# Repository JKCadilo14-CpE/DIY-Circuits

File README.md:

# DIY Circuits

A curated collection of beginner-friendly KiCad PCB projects designed for learning, experimentation, and educational reference.

This repository contains editable KiCad circuit projects for students, hobbyists, and junior engineers practicing schematic capture, PCB layout, and basic electronics documentation. Each documented project has its own README with circuit notes, source-file navigation, beginner guidance, and project-specific safety reminders.

| Repository detail | Status |
| --- | --- |
| Educational focus | Low-voltage KiCad PCB learning projects |
| KiCad metadata | KiCad 9.0 and 10.0 generator versions detected |
| Documented transistor-based projects | 12 |
| Documented project READMEs | 12 |
| Hardware-tested transistor projects | 12 |
| License | [MIT License](LICENSE) |

## Educational Use Notice

This repository is intended for educational and personal learning purposes. The circuits, schematics, PCB layouts, fabrication files, and documentation are shared to help students understand electronics design, PCB fabrication, and circuit analysis.

Please do not submit these projects as your own academic work. If you use any design or idea from this repository, make sure you understand how it works, adapt it to your own requirements, and follow your institution's academic integrity policies.

The goal of this repository is to encourage learning, experimentation, and skill development—not to replace your own design process.

## Academic Integrity

If you are using this repository for a class, use it as a reference to understand concepts and improve your own designs. Always create and submit work that complies with your instructor's requirements and your institution's academic integrity policies.

## Who This Repository Is For

- Students learning PCB design with KiCad.
- Beginners studying transistor-based circuits and simple sensor interfaces.
- Hobbyists building educational low-voltage electronics projects.
- Readers who want editable KiCad examples instead of static screenshots only.

## Repository Highlights

- Editable KiCad project, schematic, and PCB source files.
- Project-level documentation for each active documented circuit.
- Beginner-friendly notes, learning objectives, and common build checks.
- Documented prototype hardware-tested status in project READMEs.
- MIT-licensed educational reference material.

## Category Overview

| Category | Current Documentation Status | Link |
| --- | --- | --- |
| Transistor Based | Version 2.0.0 category README with 12 documented projects | [Open category](<Transistor Based/README.md>) |
| Arduino | Folder present; project documentation may be added in future phases | [Open folder](Arduino/) |
| ESP32 | Folder present; project documentation may be added in future phases | [Open folder](ESP32/) |
| Power Supply | Folder present; project documentation may be added in future phases | [Open folder](<Power Supply/>) |
| Raspberry Pi | Folder present; project documentation may be added in future phases | [Open folder](<Raspberry Pi/>) |
| Sensor Modules | Folder present; project documentation may be added in future phases | [Open folder](<Sensor Modules/>) |
| Docs | Repository documentation folder | [Open folder](Docs/) |
| Project Templates | Template/reference folder | [Open folder](<Project Templates/>) |

## Featured Projects

| Project | Why it is useful | Difficulty | Hardware Tested | Link |
| --- | --- | --- | --- | --- |
| Water Level Indicator | Multi-stage sensing and indication project with LEDs and buzzer output. | Beginner–Intermediate | Yes | [Open README](<Transistor Based/water level indicator/README.md>) |
| Temperature Controlled DC Fan - BC547 | Thermistor-based fan-control example using a transistor driver stage. | Beginner | Yes | [Open README](<Transistor Based/temperature controlled dc fan - BC547/README.md>) |
| Automatic Hand Sanitizer | Sensor-controlled pump-switching project for load-control practice. | Intermediate | Yes | [Open README](<Transistor Based/automatic hand sanitizer/README.md>) |
| Laser Alarm Security Circuit | Optical interruption alarm example using an LDR, LED, and buzzer. | Intermediate | Yes | [Open README](<Transistor Based/Laser Alarm Security Circuit/README.md>) |
| Astable Multivibrator Circuit | Classic two-transistor LED flasher for timing and feedback concepts. | Beginner | Yes | [Open README](<Transistor Based/astable miltivibrator Circuit/README.md>) |
| 9V Battery Status Indicator Circuit | Simple voltage-indicator project using LEDs, zener reference, and transistors. | Beginner | Yes | [Open README](<Transistor Based/9V Battery Status Indicator Circuit/README.md>) |

## Complete Project Catalog

The Version 2.0.0 documented project catalog currently covers the transistor-based category.

| Project | Category | Difficulty | Hardware Tested | Documentation | Link |
| --- | --- | --- | --- | --- | --- |
| 9V Battery Status Indicator Circuit | Voltage indication | Beginner | Yes | README available | [Open](<Transistor Based/9V Battery Status Indicator Circuit/README.md>) |
| Astable Multivibrator Circuit | Timing / oscillator | Beginner | Yes | README available | [Open](<Transistor Based/astable miltivibrator Circuit/README.md>) |
| Light-Activated Switch Circuit | Light-activated switching | Beginner | Yes | README available | [Open](<Transistor Based/Light-Activated Switch Circuit/README.md>) |
| Temperature Controlled DC Fan - BC547 | Temperature control | Beginner | Yes | README available | [Open](<Transistor Based/temperature controlled dc fan - BC547/README.md>) |
| Laser Alarm Security Circuit | Optical alarm | Intermediate | Yes | README available | [Open](<Transistor Based/Laser Alarm Security Circuit/README.md>) |
| Fire Alarm System Using Photodiode | Optical alarm | Intermediate | Yes | README available | [Open](<Transistor Based/fire alarm system using photodiode/README.md>) |
| Obstacle Detector | IR obstacle sensing | Intermediate | Yes | README available | [Open](<Transistor Based/obstacle detector/README.md>) |
| Touch Sensor Circuit | Touch sensing | Beginner–Intermediate | Yes | README available | [Open](<Transistor Based/touch sensor circuit/README.md>) |
| Clap Switch Circuit | Sound-triggered switching | Intermediate | Yes | README available | [Open](<Transistor Based/clap switch circuit/clap switch circuit/README.md>) |
| Automatic Hand Sanitizer | Sensor-controlled load | Intermediate | Yes | README available | [Open](<Transistor Based/automatic hand sanitizer/README.md>) |
| Hidden Wire Detector | Detection / sensing | Intermediate | Yes | README available | [Open](<Transistor Based/Hidden Wire Detector/README.md>) |
| Water Level Indicator | Water-level sensing | Beginner–Intermediate | Yes | README available | [Open](<Transistor Based/water level indicator/README.md>) |

## Learning Path

Start with the simpler indicator and timing circuits, then move into sensor-driven and multi-stage projects:

1. 9V Battery Status Indicator Circuit
2. Astable Multivibrator Circuit
3. Light-Activated Switch Circuit
4. Temperature Controlled DC Fan - BC547
5. Laser Alarm Security Circuit
6. Fire Alarm System Using Photodiode
7. Obstacle Detector
8. Touch Sensor Circuit
9. Clap Switch Circuit
10. Automatic Hand Sanitizer
11. Hidden Wire Detector
12. Water Level Indicator

See the [Transistor Based category README](<Transistor Based/README.md>) for the category index, common build checks, and category-level safety notes.

## Repository Statistics

| Statistic | Detected value |
| --- | --- |
| Documented transistor-based projects | 12 |
| Project READMEs in `Transistor Based/` | 12 |
| Hardware-tested transistor projects | 12 |
| KiCad generator versions | 9.0, 10.0 |
| License file | MIT License present |
| Circuit categories | Voltage indication, timing, light sensing, optical alarm, IR sensing, touch sensing, sound switching, load control, wire detection, water-level sensing |

## Future Roadmap

- Add more finished hardware photographs where available.
- Continue improving project galleries and 3D board renders.
- Add BOMs, assembly notes, and manufacturing packages in a later release phase.
- Expand educational explanations without duplicating project READMEs.
- Extend Version 2.0.0 documentation standards to additional repository categories after review.

## Contributing

Documentation improvements, educational suggestions, bug reports, and pull requests are welcome. Please keep changes clear, evidence-based, and beginner-friendly.

## Safety

These projects are intended for low-voltage electronics learning. Do not connect them to mains electricity or use them as certified alarm, safety, medical, life-support, or mission-critical equipment. Review each design carefully before building or modifying it.

## License

This repository is available under the [MIT License](LICENSE).

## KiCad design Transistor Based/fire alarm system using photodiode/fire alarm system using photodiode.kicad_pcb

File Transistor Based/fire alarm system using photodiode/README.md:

# Fire Alarm System Using Photodiode

A beginner-friendly photodiode alarm project that demonstrates how light from a flame can activate a transistor-driven LED and buzzer output.

## Project Information

| Item | Details |
| --- | --- |
| Status | Educational Prototype |
| Difficulty | Intermediate |
| Hardware Tested | Breadboard and PCB prototype assembled and functionally tested |
| Supply Voltage | Prototype tested with a 9V battery; exact operating range not characterized |
| KiCad Compatibility | KiCad 10.0 metadata |
| License | MIT License |

## Project Overview

This project demonstrates an educational optical fire-alarm concept using a photodiode, BC547 transistor, LED, and buzzer. Light from a flame reaches the photodiode, the photodiode changes the sensing condition, the transistor stage responds, and the LED/buzzer output path activates.

This README documents the photodiode implementation shown in the KiCad schematic. A thermistor-based version could be explored as a future modification, but this README documents the verified photodiode implementation.

This project is intended for educational demonstration only and must not be relied upon as a fire detection, fire alarm, or life-safety device.

## Features

- Photodiode-based optical sensing input.
- Single BC547 transistor stage.
- LED visual output.
- Buzzer audible output.
- Beginner-friendly example of sensor polarity, transistor orientation, and resistor verification.
- Existing schematic, PCB layout images, 3D render, editable KiCad files, and B.Cu PDF export.

## Applications

- Educational photodiode alarm demonstrations.
- Introductory transistor switching exercises.
- Low-voltage optical sensor laboratory activities.
- Breadboard-to-PCB comparison practice.
- Soldering, continuity, and cold-joint troubleshooting exercises.
- Demonstrations of how ambient light can influence optical sensor circuits.

## Components Used

| Reference | Component | Role in the Circuit |
| --- | --- | --- |
| J1 | `input` connector | Provides the circuit input connection shown in the schematic. |
| BZ1 | Buzzer | Audible output device in the alarm output path. |
| D1 | LED | Visual output indicator. |
| D2 | `D_Photo` photodiode | Optical sensor input that responds to light reaching its surface. |
| Q1 | BC547 transistor | Transistor stage that responds to the photodiode sensing condition. |
| R1 | Schematic resistor value | Resistor in the sensing/output network; use the value documented in the schematic for the verified build. |

## Circuit Explanation

The schematic uses D2 as the photodiode input. When light reaches the photodiode, the sensing condition changes and affects the bias at Q1.

Q1 is a BC547 transistor stage connected to the LED and buzzer output path. When the transistor stage responds to the photodiode condition, D1 and BZ1 provide visible and audible indication.

R1 is shown in the schematic with its documented value. Because the schematic label is the repository evidence for this build, verify the resistor value against the schematic before assembly instead of guessing or substituting parts.

This circuit is an educational optical alarm demonstration. It does not document a measured flame-detection distance, sensing angle, response time, temperature threshold, light-intensity threshold, or output current.

## Theory

A photodiode is a light-sensitive semiconductor device. In this project, it is used as the optical input device for a transistor alarm stage. Light from a flame can reach the photodiode and change the condition applied to the transistor stage.

A BC547 transistor can be used as a small-signal switching stage. The transistor does not measure fire or temperature directly; it responds to the electrical condition created by the photodiode and surrounding resistor network.

Ambient light can also influence a photodiode. This is why testing should be performed under controlled indoor lighting, and why unwanted LED glow can be diagnosed by covering the photodiode.

The photodiode approach is different from a temperature-based alarm. A thermistor-based version could be explored as a future modification, but this README documents the verified photodiode implementation.

## How It Works

1. A 9V battery is connected to J1 with correct polarity.
2. The photodiode is exposed to the intended optical test source.
3. Light from a flame reaches the photodiode.
4. The photodiode changes the sensing condition at the transistor stage.
5. Q1 responds to that sensing condition.
6. The LED and buzzer output path activates.

This section describes the intended photodiode alarm concept from the schematic. Physical prototype observations, including flashlight activation during testing, are documented separately under **Verified Prototype Observations**.

## Project Gallery

### Schematic

### PCB Layout Top

### PCB Layout Bottom

### 3D PCB Render

### Finished Hardware

> Finished hardware photographs will be added after the completed prototype is photographed.

## Assembly Guide

1. Review the schematic and PCB layout before soldering.
2. Install R1 after verifying the resistor value against the schematic.
3. Install D2, confirming photodiode polarity.
4. Install D1, confirming LED polarity.
5. Install Q1 after checking the BC547 emitter, base, and collector pinout.
6. Install BZ1, confirming the selected buzzer is appropriate for the build.
7. Install the input connector.
8. Inspect all solder joints and PCB copper traces before applying power.
9. Perform continuity checks before connecting the battery.

## Before You Power the Circuit

| Check | What to Verify |
| --- | --- |
| Battery polarity | Confirm correct supply polarity before connection. |
| Transistor orientation | Confirm Q1 matches the BC547 pinout expected by the PCB footprint. |
| Photodiode polarity | Confirm D2 orientation before applying power. |
| LED polarity | Confirm D1 anode/cathode orientation. |
| Resistor value | Verify R1 against the schematic before assembly. |
| Buzzer connection | Confirm BZ1 is connected in the intended output location. |
| PCB copper traces | Inspect for oxidation, contamination, or visible damage. |
| Solder bridges | Inspect adjacent pads and traces for accidental shorts. |
| Continuity test | Check for unintended shorts before connecting a battery. |

## Testing

This project is intended for educational demonstration only and must not be relied upon as a fire detection, fire alarm, or life-safety device. Flame testing should be performed only with a small controlled flame source, appropriate supervision, and safe surroundings.

Suggested test procedure:

1. Inspect the PCB under good lighting.
2. Confirm 9V battery polarity before connection.
3. Check battery voltage with a multimeter if behavior is inconsistent.
4. Verify Q1 transistor orientation.
5. Verify D2 photodiode polarity.
6. Verify D1 LED polarity.
7. Verify the R1 value against the schematic.
8. Test indoors under controlled lighting before introducing a flame source.
9. Perform a conservative flame-response demonstration and observe the LED/buzzer response.
10. Use a mobile phone flashlight only as a prototype-observed optical response check, not as the intended design description.
11. Evaluate whether ambient light causes unwanted LED glow or false triggering.
12. Compare PCB behavior with the verified breadboard prototype if unexpected behavior occurs.
13. Disconnect power immediately if any component becomes unusually warm.

Successful test indicators:

- The board powers without short-circuit symptoms.
- The circuit responds during the intended educational optical demonstration.
- Unwanted LED glow can be explained by ambient light rather than a wiring fault.
- PCB behavior is consistent with the breadboard prototype after assembly issues are corrected.

## Practical Build Notes

### Prototype Notes

The following items are **Verified Prototype Observations** from the physical build. They extend beyond what is explicitly guaranteed by the KiCad schematic.

- Breadboard prototype required several rounds of troubleshooting before operating correctly.
- Incorrect resistor selection and wiring mistakes that affected the intended circuit power distribution initially prevented proper operation.
- Breadboard prototype eventually operated as intended.
- PCB prototype was assembled and successfully tested.
- Prototype was powered using a 9V battery.
- During prototype testing, light from a flame activated the circuit.
- During prototype testing, a mobile phone flashlight also activated the circuit.
- PCB prototype initially experienced photodiode sensitivity issues and cold solder joints.
- During prototype testing, increasing the resistor value associated with the photodiode sensing stage reduced unwanted triggering caused by ambient light in this specific prototype.
- During prototype testing, the LED occasionally glowed dimly because the photodiode responded to surrounding light.
- Covering the photodiode removed the unwanted LED illumination, indicating that surrounding ambient light not a wiring fault was causing the unwanted sensor response during prototype testing.

### Photodiode Sensitivity Notes

Photodiodes may respond to surrounding ambient light. Test indoors under controlled lighting conditions, and avoid direct sunlight or other intense light sources that may cause unintended activation.

The resistor-value change described above is a verified prototype observation, not the documented schematic configuration. Retain the resistor value shown in the schematic unless intentionally redesigning and revalidating the sensing stage.

This README does not recommend resistor substitutions.

### Photodiode vs Thermistor Note

A thermistor-based version could be explored as a future modification, but this README documents the verified photodiode implementation.

Do not assume a thermistor version has been verified for this project unless a future schematic, PCB, and tested prototype explicitly document that change.

### Builder Recommendations

- Verify transistor orientation using the datasheet.
- Verify photodiode polarity and LED polarity before soldering.
- Verify the resistor value against the schematic before assembly. Use the documented schematic value for the verified build.
- Breadboard-test before PCB assembly whenever possible.
- Inspect solder joints carefully.
- Inspect PCB copper traces for oxidation, contamination, or damage.
- Compare PCB behavior with the verified breadboard prototype.
- Make only one circuit modification at a time during troubleshooting, then retest before changing additional components.
- If the LED glows dimly unexpectedly, cover the photodiode to determine whether ambient light is influencing the circuit.
- Disconnect power immediately if components become unusually warm, then verify polarity, transistor orientation, resistor value, and solder quality before testing again.

## Troubleshooting

| Symptom | Checks |
| --- | --- |
| Circuit does not respond to flame | Check battery polarity and voltage, photodiode polarity, Q1 orientation, R1 value, solder joints, and whether the flame test is safely positioned for the photodiode to receive light. |
| Circuit responds to flashlight but not flame | Recheck the flame demonstration setup, photodiode orientation, ambient lighting, and breadboard comparison; do not infer a certified fire-detection capability. |
| LED glows dimly without a flame | Cover the photodiode completely, reduce ambient lighting, verify photodiode polarity, inspect the resistor value associated with the photodiode sensing stage, check solder joints, and compare behavior with the verified breadboard prototype. |
| False triggering from ambient light | Test under controlled indoor lighting, avoid direct sunlight or intense light sources, and cover the photodiode to confirm whether ambient light is influencing the circuit. |
| Incorrect transistor orientation | Check the BC547 datasheet and confirm emitter, base, and collector match the PCB footprint. |
| Incorrect photodiode polarity | Confirm D2 orientation and reinstall correctly if needed. |
| Wrong resistor value | Verify R1 against the schematic and compare with the breadboard prototype. |
| Cold solder joints | Reinspect dull, cracked, or incomplete solder joints after disconnecting power. |
| Breadboard works but PCB does not | Compare PCB assembly against the verified breadboard prototype, then inspect solder bridges, cold solder joints, copper trace condition, component polarity, and resistor placement. |
| Buzzer or LED output does not activate | Check BZ1 and D1 connections, Q1 orientation, photodiode polarity, R1 value, solder joints, and battery condition. |

If covering the photodiode completely causes the LED to turn off, the sensor is responding to ambient light rather than a wiring fault.

## Downloads

| File | Description |
| --- | --- |
| [`fire alarm system using photodiode.kicad_pro`](<fire alarm system using photodiode.kicad_pro>) | KiCad project file. Open this file in KiCad. |
| [`fire alarm system using photodiode.kicad_sch`](<fire alarm system using photodiode.kicad_sch>) | KiCad schematic source. |
| [`fire alarm system using photodiode.kicad_pcb`](<fire alarm system using photodiode.kicad_pcb>) | KiCad PCB layout source. |
| [`fire alarm system using photodiode-B_Cu.pdf`](<fire alarm system using photodiode-B_Cu.pdf>) | Existing B.Cu PDF plot export. |

## Educational Use Notice

This repository is intended for educational and personal learning purposes. The circuits, schematics, PCB layouts, fabrication files, and documentation are shared to help students understand electronics design, PCB fabrication, and circuit analysis.

Please do not submit these projects as your own academic work. If you use any design or idea from this repository, make sure you understand how it works, adapt it to your own requirements, and follow your institution's academic integrity policies.

The goal of this repository is to encourage learning, experimentation, and skill development—not to replace your own design process.

## Academic Integrity

If you are using this repository for a class, use it as a reference to understand concepts and improve your own designs. Always create and submit work that complies with your instructor's requirements and your institution's academic integrity policies.

## Revision History

| Version | Changes |
| --- | --- |
| 2.0.0 | Updated README to follow the Version 2.0.0 documentation standard with expanded project information, circuit explanation, theory, assembly guidance, testing notes, practical build notes, troubleshooting, gallery, downloads, and repository notices. |

## License

This project is released under the MIT License. See the repository [LICENSE](../../LICENSE).

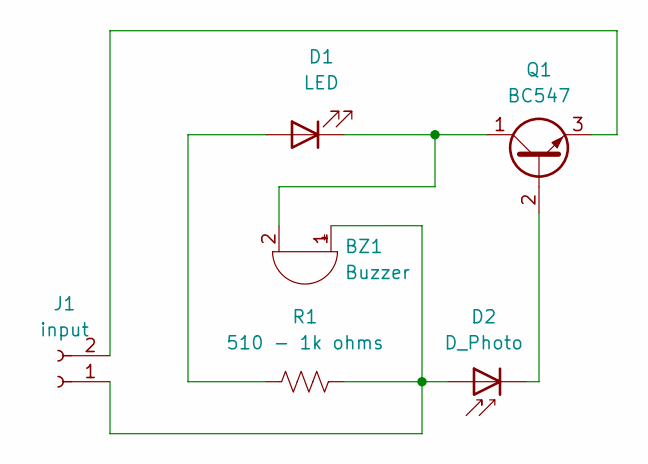
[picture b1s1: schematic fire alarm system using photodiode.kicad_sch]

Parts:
BZ1: Buzzer; Buzzer_15x7.5RM7.6
D1: LED; LED_D5.0mm
D2: D_Photo; LED_D5.0mm_IRBlack
J1: input; TerminalBlock_Phoenix_MKDS-1,5-2_1x02_P5.00mm_Horizontal
Q1: BC547; TO-92_Inline
R1: 510 - 1k ohms; R_Axial_DIN0207_L6.3mm_D2.5mm_P10.16mm_Horizontal

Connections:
unnamed: BZ1.1 (+), D2.2 (A), J1.1, R1.2
unnamed: BZ1.2 (-), D1.1 (K), Q1.1 (C)
unnamed: D1.2 (A), R1.1
unnamed: D2.1 (K), Q1.2 (B)
unnamed: J1.2, Q1.3 (E)

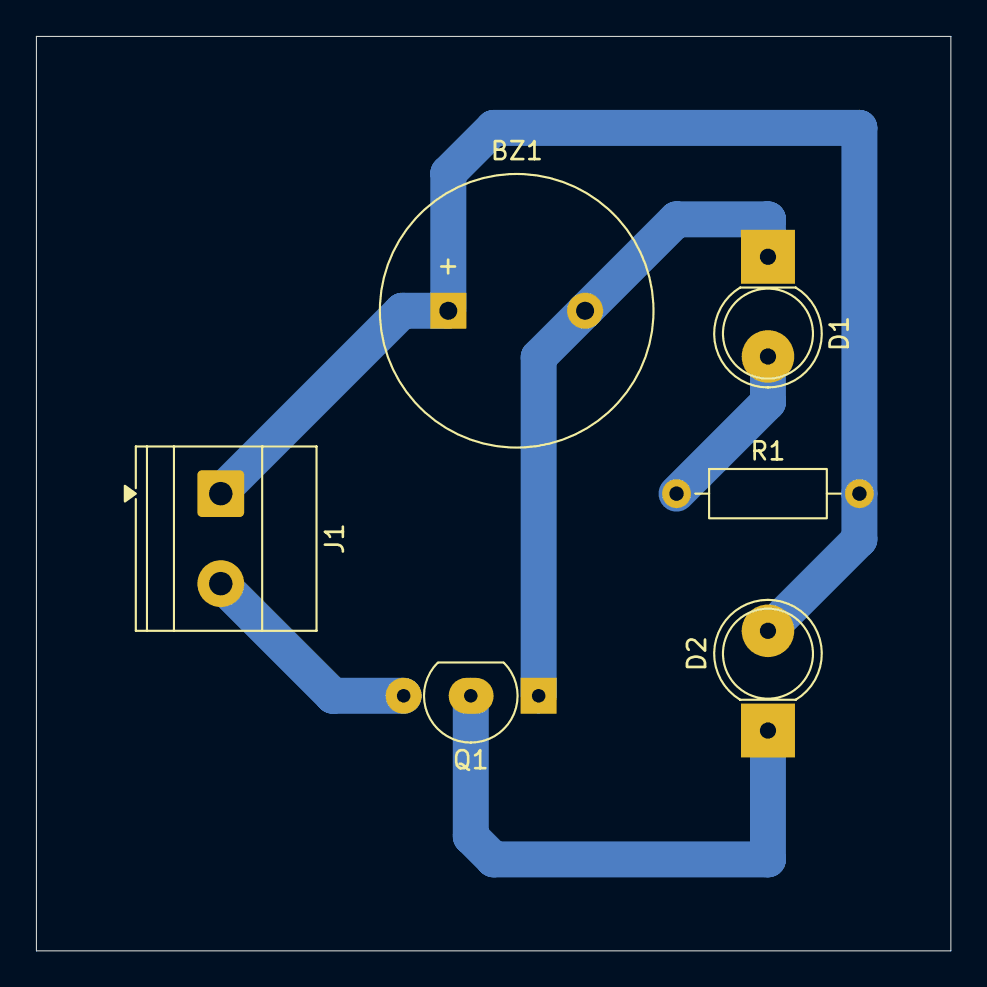
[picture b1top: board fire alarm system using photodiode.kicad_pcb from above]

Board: 2 copper layers, 50.8 x 50.8 mm, 6 parts (0 on the bottom side), 5 nets.

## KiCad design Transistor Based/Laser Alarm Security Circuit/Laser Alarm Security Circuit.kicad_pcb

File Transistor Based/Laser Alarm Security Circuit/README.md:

# Laser Alarm Security Circuit

A beginner-friendly laser-interruption alarm project using an LDR, BC547 transistor, LED, buzzer, and an external laser source for demonstration.

## Project Information

| Item | Details |
| --- | --- |
| Status | Educational Prototype |
| Difficulty | Intermediate |
| Hardware Tested | Breadboard and PCB prototype assembled and functionally tested |
| Supply Voltage | Prototype tested with a 9V battery; exact operating range not characterized |
| KiCad Compatibility | KiCad 10.0 metadata |
| License | MIT License |

## Project Overview

This project demonstrates an educational optical beam-interruption alarm. An external laser module projects a beam onto the LDR. The LDR and R2 form a light-dependent input condition for Q1. When the beam is interrupted, the LDR condition changes, Q1 responds, and D1/BZ1 provide visible and audible alarm indication.

The laser module used during prototype testing served only as the optical source. It is not part of the PCB schematic.

This project is intended for educational demonstration only and must not be relied upon as a real security or intrusion detection system.

## Features

- LDR-based optical sensing input.
- External laser beam used as the demonstration light source.
- Single BC547 transistor stage.
- LED visual output.
- Buzzer audible output.
- Beginner-friendly example of alignment-sensitive optical sensing.
- Existing schematic, PCB layout images, 3D render, editable KiCad files, and B.Cu PDF export.

## Applications

- Educational laser-interruption alarm demonstrations.
- LDR and fixed-resistor sensing exercises.
- Transistor switching laboratory activities.
- Optical alignment and interruption testing practice.
- Breadboard-to-PCB comparison practice.
- Soldering and cold-joint troubleshooting exercises.

## Components Used

| Reference | Component | Role in the Circuit |
| --- | --- | --- |
| J1 | `input` connector | Provides the main circuit input connection shown in the schematic. |
| J2 | `laser_input` connector | Schematic connector associated with the laser input connection. |
| R1 | `LDR03` | Light-dependent resistor used as the optical sensing element. |
| R2 | 10K ohm resistor | Fixed resistor used with the LDR to form the light-dependent input condition. |
| Q1 | BC547 transistor | Transistor stage that responds to the LDR sensing condition. |
| D1 | LED | Visual output indicator. |
| BZ1 | Buzzer | Audible output indicator. |

## Circuit Explanation

The schematic uses R1 as an LDR and R2 as a 10K ohm resistor. Together, they form a light-dependent input condition for Q1.

When the external laser beam is centered on the LDR, the LDR is illuminated and the circuit remains in its normal beam-present state. When an object interrupts the beam, the light reaching the LDR changes. That change affects the transistor stage, which drives the LED and buzzer output path.

Q1 is a BC547 transistor. Correct transistor orientation matters because the emitter, base, and collector must match the PCB footprint.

The external laser module is used as the optical source for testing and demonstration. The repository schematic documents the PCB circuit; it does not characterize laser power, detection distance, beam interruption distance, response time, or sensitivity range.

## Theory

An LDR, or light-dependent resistor, changes resistance as the light reaching its surface changes. In this project, the LDR is aimed at a laser beam so the circuit can respond when the beam is present or interrupted.

R2 works with the LDR to create a light-dependent input condition. Q1 responds to that condition and controls the output path for the LED and buzzer.

Optical alignment is important because the circuit depends on light actually reaching the LDR. A small movement of the laser or LDR can change the result, even if the electronic circuit is assembled correctly.

This project demonstrates the principle of beam interruption. It is not a certified security system and should not be used for real intrusion detection.

## How It Works

1. A 9V battery powers the PCB circuit.
2. An external laser module is powered according to its own operating-voltage requirements.
3. The laser beam is aligned so it reaches the LDR surface.
4. The LDR and R2 establish the light-dependent input condition for Q1.
5. When the beam reaches the LDR, the circuit remains in its normal beam-present state.
6. When an object interrupts the beam, the LDR condition changes.
7. Q1 responds to that change and drives D1/BZ1 for visible and audible indication.

This section describes the intended schematic operation and demonstration setup. Physical prototype observations are documented separately under **Verified Prototype Observations**.

## Project Gallery

### Schematic

### PCB Layout Top

### PCB Layout Bottom

### 3D PCB Render

### Finished Hardware

> Finished hardware photographs will be added after the completed prototype is photographed.

## Assembly Guide

1. Review the schematic and PCB layout before soldering.
2. Install R2, confirming it is 10K ohms.
3. Install R1, confirming the LDR placement.
4. Install D1, confirming LED polarity.
5. Install Q1 after checking the BC547 emitter, base, and collector pinout.
6. Install BZ1.
7. Install J1 and J2.
8. Inspect all solder joints for bridges, cold joints, and incomplete wetting.
9. Perform continuity checks before applying power.
10. Align the external laser module with the LDR during testing or after the demonstration mount is prepared.

## Before You Power the Circuit

| Check | What to Verify |
| --- | --- |
| Battery polarity | Confirm correct 9V battery polarity before connection. |
| Battery voltage | Measure the 9V battery with a multimeter before troubleshooting. |
| Laser module voltage | Confirm the laser module voltage requirement before applying power to the module. |
| Transistor orientation | Confirm Q1 matches the BC547 pinout expected by the PCB footprint. |
| LED polarity | Confirm D1 anode/cathode orientation. |
| LDR placement | Confirm R1 is installed at the LDR footprint. |
| LDR surface | Confirm the LDR surface is clean and unobstructed. |
| Resistor value | Confirm R2 is 10K ohms. |
| Solder bridges | Inspect adjacent pads and traces for accidental shorts. |
| Continuity test | Check for unintended shorts before connecting a battery. |

## Testing

This project is intended for educational demonstration only and must not be relied upon as a real security or intrusion detection system.

Suggested test procedure:

1. Inspect the PCB under good lighting.
2. Confirm battery polarity.
3. Measure the 9V battery with a multimeter to confirm the supply voltage is suitable for testing.
4. Verify the laser module operating-voltage requirement before applying power to the module.
5. Verify Q1 transistor orientation.
6. Confirm the LDR is installed and unobstructed.
7. Align the laser beam so it remains centered on the LDR.
8. Observe the normal beam-present state.
9. Interrupt the beam with an object and observe the LED/buzzer response.
10. Repeat the beam-interruption test several times.
11. Compare PCB behavior with the verified breadboard prototype if unexpected behavior occurs.
12. Disconnect power immediately if any component becomes unusually warm.

Successful test indicators:

- The PCB powers without short-circuit symptoms.
- The laser beam can be aligned onto the LDR.
- Interrupting the beam changes the output indication.
- Repeated interruption tests behave consistently when the laser and LDR remain aligned.
- PCB behavior matches the verified breadboard prototype after assembly issues are corrected.

## Practical Build Notes

### Prototype Notes

The following items are **Verified Prototype Observations** from the physical build. They extend beyond what is explicitly guaranteed by the KiCad schematic.

- Breadboard prototype operated correctly without modification.
- PCB prototype was assembled and successfully tested.
- Prototype was powered using a 9V battery.
- Minor PCB issues included cold solder joints and reversed transistor orientation.
- Correcting those assembly issues restored proper operation.
- Prototype testing used an external laser module connected to the PCB through female-to-male jumper wires.
- The laser module served only as the optical source during testing and is not part of the PCB schematic.
- The tested laser module specification indicated an operating voltage of **3.3 V to 5.0 V**.

### Laser Alignment Notes

Reliable operation depends on keeping the laser beam aligned with the LDR. Small alignment changes can affect prototype operation.

If the laser module will be mounted as part of the demonstration setup, align the laser with the LDR before permanently securing the laser module.

This README does not recommend exact alignment distances.

### Laser Module Notes

Verify the laser module's operating voltage requirements before applying power. Supplying a voltage outside the manufacturer's specified range may permanently damage the laser module.

Follow the module manufacturer's specifications when available. The tested laser module specification indicated an operating voltage of **3.3 V to 5.0 V**, but that is a verified prototype observation for the module used during testing, not a universal requirement for all laser modules.

### Builder Recommendations

- If the laser module will be mounted as part of the demonstration setup, align the laser with the LDR before permanently securing the laser module.
- Do not change resistor values unless intentionally redesigning and revalidating the circuit.
- Use a stable laser mount.
- Breadboard-test before PCB assembly whenever possible.
- Verify transistor orientation.
- Inspect solder joints carefully.
- Measure the 9V battery with a multimeter before troubleshooting to confirm the supply voltage is suitable for testing.
- Keep the laser beam centered on the LDR during testing.
- Ensure both the laser module aperture and the LDR surface are clean and unobstructed before alignment.
- Disconnect power immediately if any component becomes unusually warm, then verify component orientation before testing again.

### Laser Safety Notes

- Never look directly into the laser beam.
- Never intentionally shine the laser into another person's eyes.
- Avoid reflective surfaces that may redirect the laser beam unexpectedly during testing.
- Use the lowest practical laser power suitable for demonstration.
- Disconnect power before adjusting laser alignment.
- Do not use this project as a real security system.

## Troubleshooting

| Symptom | Checks |
| --- | --- |
| Alarm never activates | Check battery polarity and voltage, laser module power, laser alignment, LDR position, Q1 orientation, D1 polarity, BZ1 connection, solder joints, and resistor value. |
| Alarm always remains active | Confirm the laser beam reaches the LDR, check that the LDR surface is clean, inspect Q1 orientation, and look for solder bridges or cold solder joints. |
| Alarm activates intermittently | Verify the laser beam remains centered on the LDR, check that the laser mount has not shifted, inspect solder joints, and verify battery voltage. |
| Laser beam misses the LDR | Realign the laser and LDR, then repeat the interruption test. |
| Incorrect transistor orientation | Check the BC547 datasheet and confirm emitter, base, and collector match the PCB footprint. |
| Cold solder joints | Reinspect dull, cracked, or incomplete solder joints after disconnecting power. |
| Breadboard works but PCB does not | Compare PCB assembly against the verified breadboard prototype, then inspect solder bridges, cold solder joints, component placement, and transistor orientation. |
| Incorrect battery voltage | Measure the 9V battery with a multimeter and replace it if it is not suitable for testing. |
| Laser module does not illuminate | Verify laser module supply voltage, wiring, and module polarity before continuing. |
| Incorrect laser module supply voltage | Disconnect power and verify the module manufacturer's voltage specification before reconnecting. |

## Downloads

| File | Description |
| --- | --- |
| [`Laser Alarm Security Circuit.kicad_pro`](<Laser Alarm Security Circuit.kicad_pro>) | KiCad project file. Open this file in KiCad. |
| [`Laser Alarm Security Circuit.kicad_sch`](<Laser Alarm Security Circuit.kicad_sch>) | KiCad schematic source. |
| [`Laser Alarm Security Circuit.kicad_pcb`](<Laser Alarm Security Circuit.kicad_pcb>) | KiCad PCB layout source. |
| [`Laser Alarm Security Circuit-B_Cu.pdf`](<Laser Alarm Security Circuit-B_Cu.pdf>) | Existing B.Cu PDF plot export. |

## Educational Use Notice

This repository is intended for educational and personal learning purposes. The circuits, schematics, PCB layouts, fabrication files, and documentation are shared to help students understand electronics design, PCB fabrication, and circuit analysis.

Please do not submit these projects as your own academic work. If you use any design or idea from this repository, make sure you understand how it works, adapt it to your own requirements, and follow your institution's academic integrity policies.

The goal of this repository is to encourage learning, experimentation, and skill development—not to replace your own design process.

## Academic Integrity

If you are using this repository for a class, use it as a reference to understand concepts and improve your own designs. Always create and submit work that complies with your instructor's requirements and your institution's academic integrity policies.

## Revision History

| Version | Changes |
| --- | --- |
| 2.0.0 | Updated README to follow the Version 2.0.0 documentation standard with expanded project information, circuit explanation, theory, assembly guidance, testing notes, practical build notes, troubleshooting, gallery, downloads, and repository notices. |

## License

This project is released under the MIT License. See the repository [LICENSE](../../LICENSE).

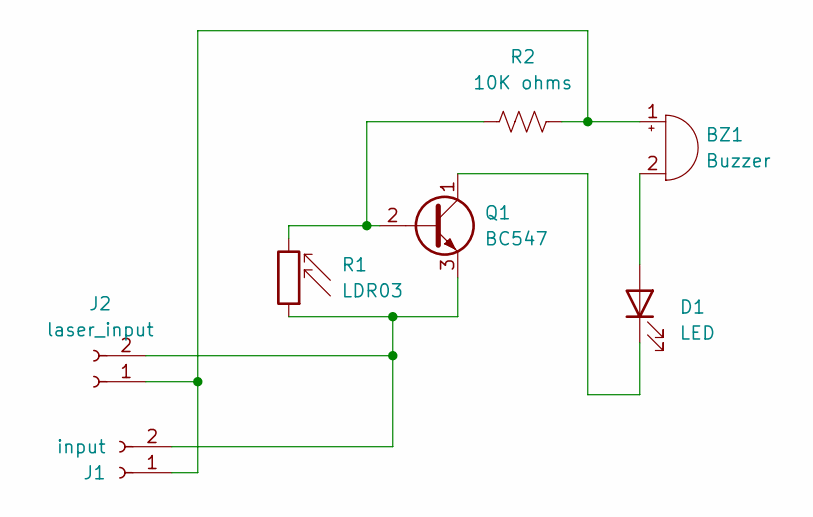
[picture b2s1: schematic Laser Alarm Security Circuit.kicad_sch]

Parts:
BZ1: Buzzer; Buzzer_15x7.5RM7.6
D1: LED; LED_D5.0mm
J1: input; TerminalBlock_Phoenix_MKDS-1,5-2_1x02_P5.00mm_Horizontal
J2: laser_input; TerminalBlock_Phoenix_MKDS-1,5-2_1x02_P5.00mm_Horizontal
Q1: BC547; TO-92_Inline
R1: LDR03; R_LDR_10x8.5mm_P7.6mm_Vertical
R2: 10K ohms; R_Axial_DIN0207_L6.3mm_D2.5mm_P10.16mm_Horizontal

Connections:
unnamed: BZ1.1 (+), J1.1, J2.1, R2.2
unnamed: BZ1.2 (-), D1.2 (A)
unnamed: D1.1 (K), Q1.1 (C)
unnamed: J1.2, J2.2, Q1.3 (E), R1.1
unnamed: Q1.2 (B), R1.2, R2.1

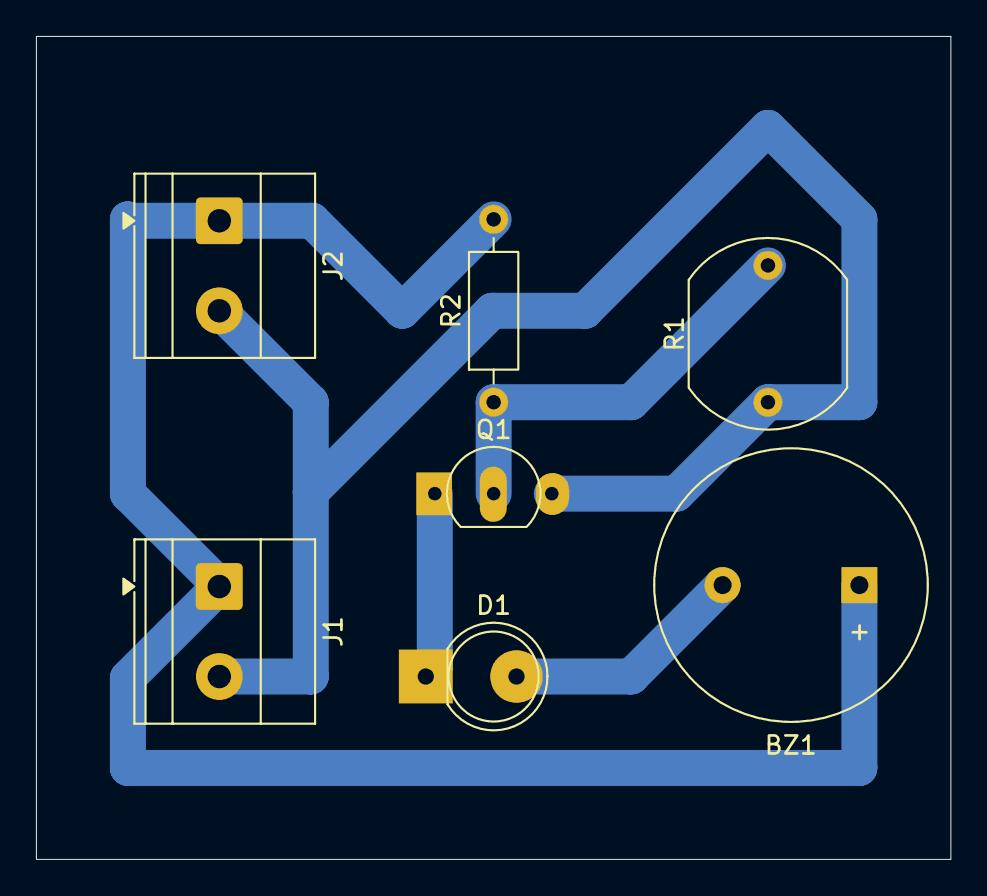
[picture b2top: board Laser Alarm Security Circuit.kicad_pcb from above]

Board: 2 copper layers, 50.8 x 45.7 mm, 7 parts (0 on the bottom side), 5 nets.

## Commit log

2026-06-14 Added Water Level Indicator Project
2026-06-14 Added Temperature controlled DC fan project
2026-06-15 Added Touch Sensor Circuit
2026-06-15 Added Clap Switch Circuit
2026-06-15 Added Fire Alarm System using Photodiode
2026-06-15 Added Hidden Wire Detector
2026-06-15 Added Obstacle Detector Circuit
2026-06-15 Added Fire alarm Circuit Using Photodiode
2026-06-15 Added 9V Battery Status Indicator Circuit
2026-06-15 Added Laser Alarm Security Circuit
2026-06-15 Added Light-Activated Switch Circuit
2026-06-15 Added automatic hand sanitizer Circuit
2026-06-15 Added astable milti-vibrator Circuit
2026-06-26 Clean KiCad repository artifacts and add documentation scaffold
2026-06-26 Enhance KiCad project documentation
2026-06-26 Enhance README with educational use and integrity notice
    Added educational use notice and academic integrity guidelines to README.
2026-06-27 Improve repository documentation and portfolio
2026-06-27 Add project gallery images
2026-06-28 Release DIY-Circuits v2.0.0
2026-06-28 Enhance README with project badges
    Added badges for release, license, KiCad version, projects count, hardware testing, and documentation version.
